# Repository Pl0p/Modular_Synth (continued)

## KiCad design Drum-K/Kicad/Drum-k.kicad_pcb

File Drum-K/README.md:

# Drum_K
Analogue drum kick

## Controls are :

 - Soft/Hard attack
 - Decay
 - Tune
 - Distortion
 - 

### Inputs

 - Kick trigger
 - [ ] Decay CV
 - [ ] Tune CV

# [Here is the schematic](https://github.com/Pl0p/Modular_Synth/blob/main/Drum-K/Drum-k.pdf)

### Front of the PCB 

### Back of the PCB

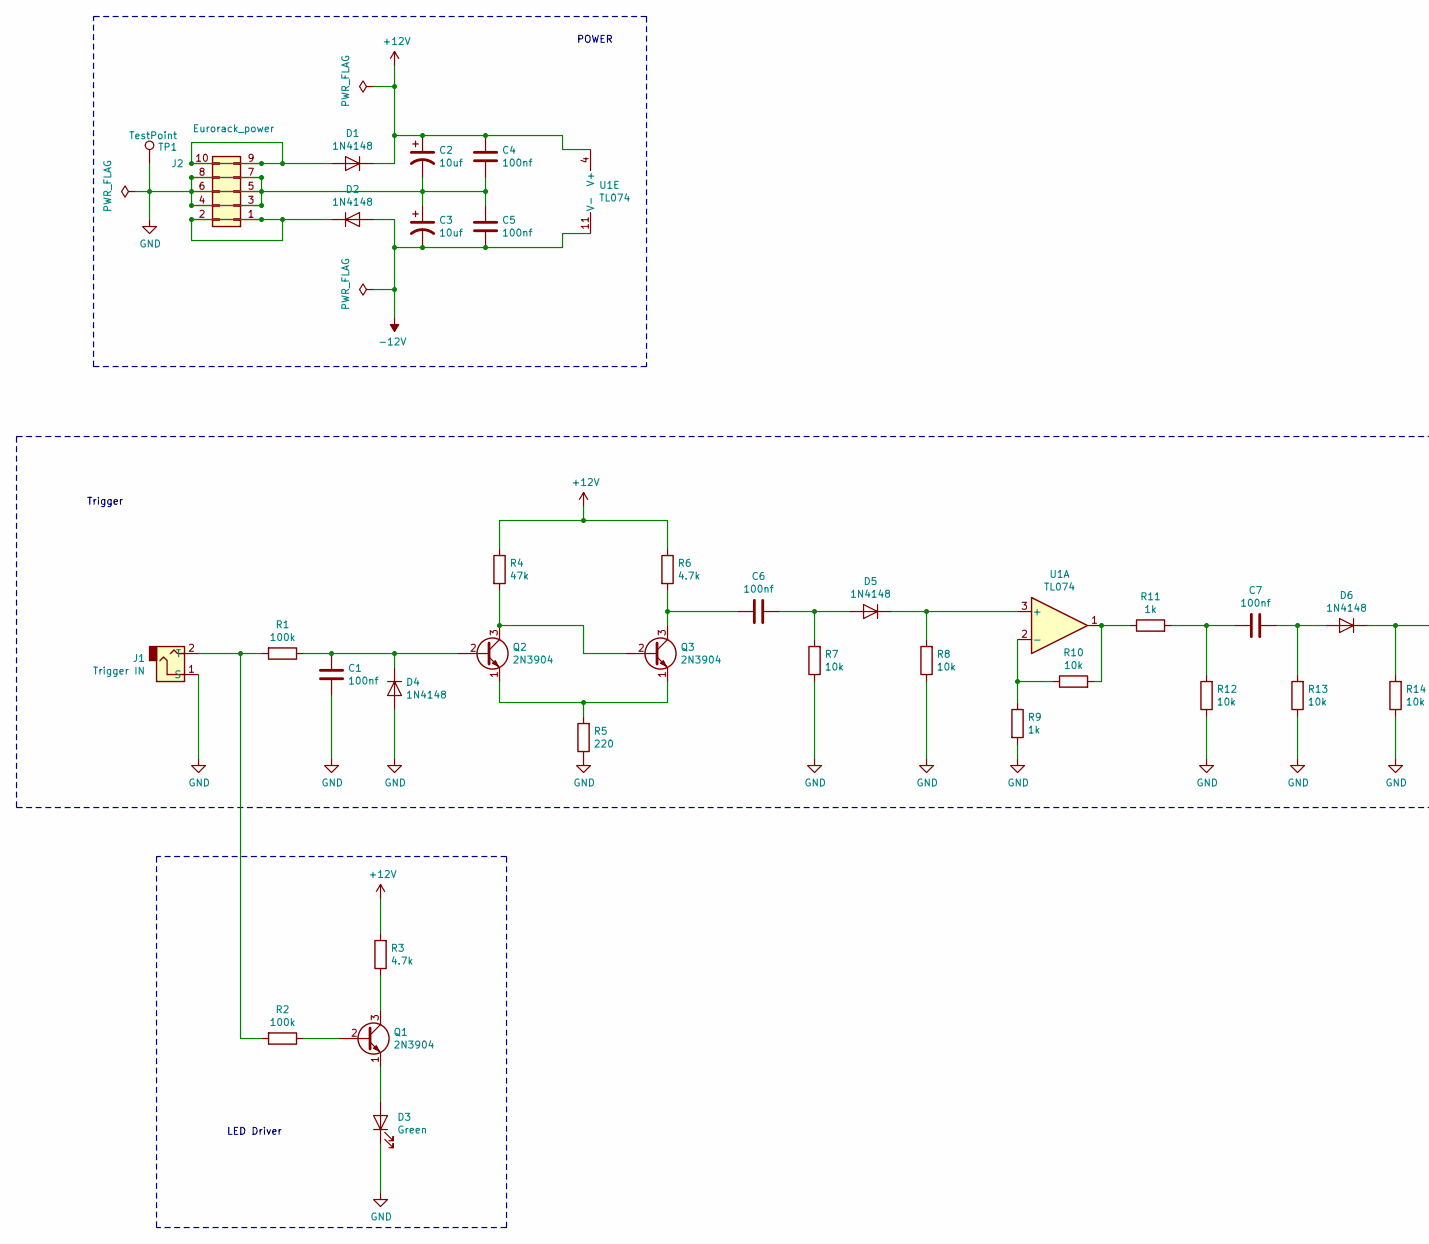
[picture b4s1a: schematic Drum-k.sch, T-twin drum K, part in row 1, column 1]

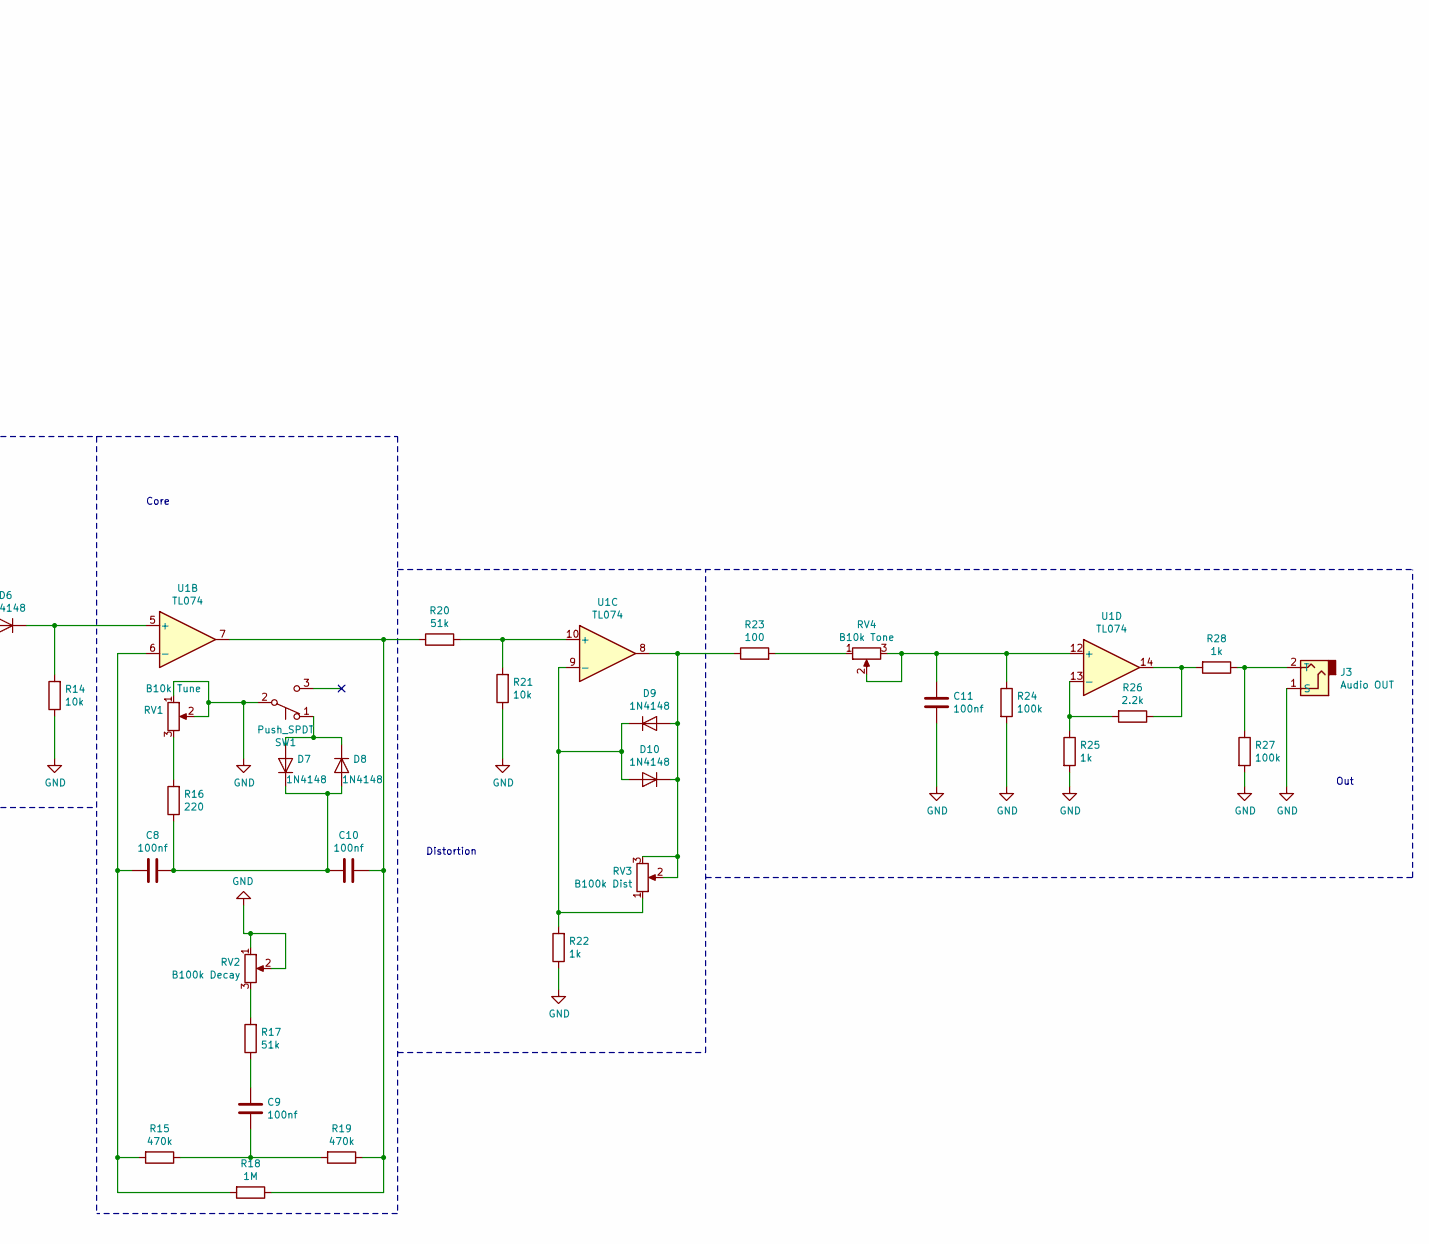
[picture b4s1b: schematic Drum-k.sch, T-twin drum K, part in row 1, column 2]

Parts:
C1, C4, C5, C6, C7, C8, C9, C10, C11: 100nf; C_Disc_(100nf_ceramique)
C2, C3: 10uf; C_Radial_10uf_50v(5*11)
D1, D2, D4, D5, D6, D7, D8, D9, D10: 1N4148; Diode1N4148
D3: Green; LED_5.0mm
J1: Trigger IN; SolderWirePad_1x02_Drill1.5mm
J2: Eurorack_power; 2X05_Power_conn
J3: Audio OUT; SolderWirePad_1x02_Drill1.5mm
Q1, Q2, Q3: 2N3904; Transistor
R1, R2, R24, R27: 100k; Resistance
R3, R6: 4.7k; Resistance
R4: 47k; Resistance
R5, R16: 220; Resistance
R7, R8, R10, R12, R13, R14, R21: 10k; Resistance
R9, R11, R22, R25, R28: 1k; Resistance
R15, R19: 470k; Resistance
R17, R20: 51k; Resistance
R18: 1M; Resistance
R23: 100; Resistance
R26: 2.2k; Resistance
RV1: B10k Tune; Pot_WH148-1A2
RV2: B100k Decay; Pot_WH148-1A2
RV3: B100k Dist; Pot_WH148-1A2
RV4: B10k Tone; Pot_WH148-1A2
SW1: Push_SPDT; SolderWirePad_1x02_+1NC_Drill1.5m
TP1: TestPoint; TestPoint_Pad_3.0x3.0mm
U1: TL074; DIP14-Socket

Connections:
+12V: C2.1, C4.1, D1.1 (K), R3.2, R4.1, R6.1, U1.4 (V+)
-12V: C3.2, C5.2, D2.2 (A), U1.11 (V-)
GND: C1.2, C2.2, C3.1, C4.2, C5.1, C11.2, D3.1 (K), D4.2 (A), J1.1 (S), J2.3, J2.4, J2.5, J2.6, J2.7, J2.8, J3.1 (S), R5.1, R7.1, R8.1, R9.2, R12.1, R13.1, R14.1, R21.1, R22.1, R24.2, R25.2, R27.2, RV1.1, RV1.2, RV2.1, RV2.2, SW1.2 (B), TP1.1
unnamed: C1.1, D4.1 (K), Q2.2 (B), R1.1
unnamed: C6.1, D5.2 (A), R7.2
unnamed: C6.2, Q3.3 (C), R6.2
unnamed: C7.1, D6.2 (A), R13.2
unnamed: C7.2, R11.2, R12.2
unnamed: C8.2, R15.2, R18.2, U1.6 (-)
unnamed: C9.1, R15.1, R19.2
unnamed: C9.2, R17.1
unnamed: C10.1, R18.1, R19.1, R20.1, U1.7
unnamed: C8.1, C10.2, D7.1 (K), D8.2 (A), R16.1
unnamed: C11.1, R24.1, RV4.2, RV4.3, U1.12 (+)
unnamed: D1.2 (A), J2.9, J2.10
unnamed: D2.1 (K), J2.1, J2.2
unnamed: D3.2 (A), Q1.1 (E)
unnamed: D5.1 (K), R8.2, U1.3 (+)
unnamed: D6.1 (K), R14.2, U1.5 (+)
unnamed: D7.2 (A), D8.1 (K), SW1.1 (A)
unnamed: D9.2 (A), D10.1 (K), R23.1, RV3.2, RV3.3, U1.8
unnamed: D9.1 (K), D10.2 (A), R22.2, RV3.1, U1.9 (-)
unnamed: J1.2 (T), R1.2, R2.2
unnamed: J3.2 (T), R27.1, R28.1
unnamed: Q1.2 (B), R2.1
unnamed: Q1.3 (C), R3.1
unnamed: Q2.1 (E), Q3.1 (E), R5.2
unnamed: Q2.3 (C), Q3.2 (B), R4.2
unnamed: R9.1, R10.1, U1.2 (-)
unnamed: R10.2, R11.1, U1.1
unnamed: R16.2, RV1.3
unnamed: R17.2, RV2.3
unnamed: R20.2, R21.2, U1.10 (+)
unnamed: R23.2, RV4.1
unnamed: R25.1, R26.2, U1.13 (-)
unnamed: R26.1, R28.2, U1.14

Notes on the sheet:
POWER
Trigger
LED Driver
Core
Distortion
Out

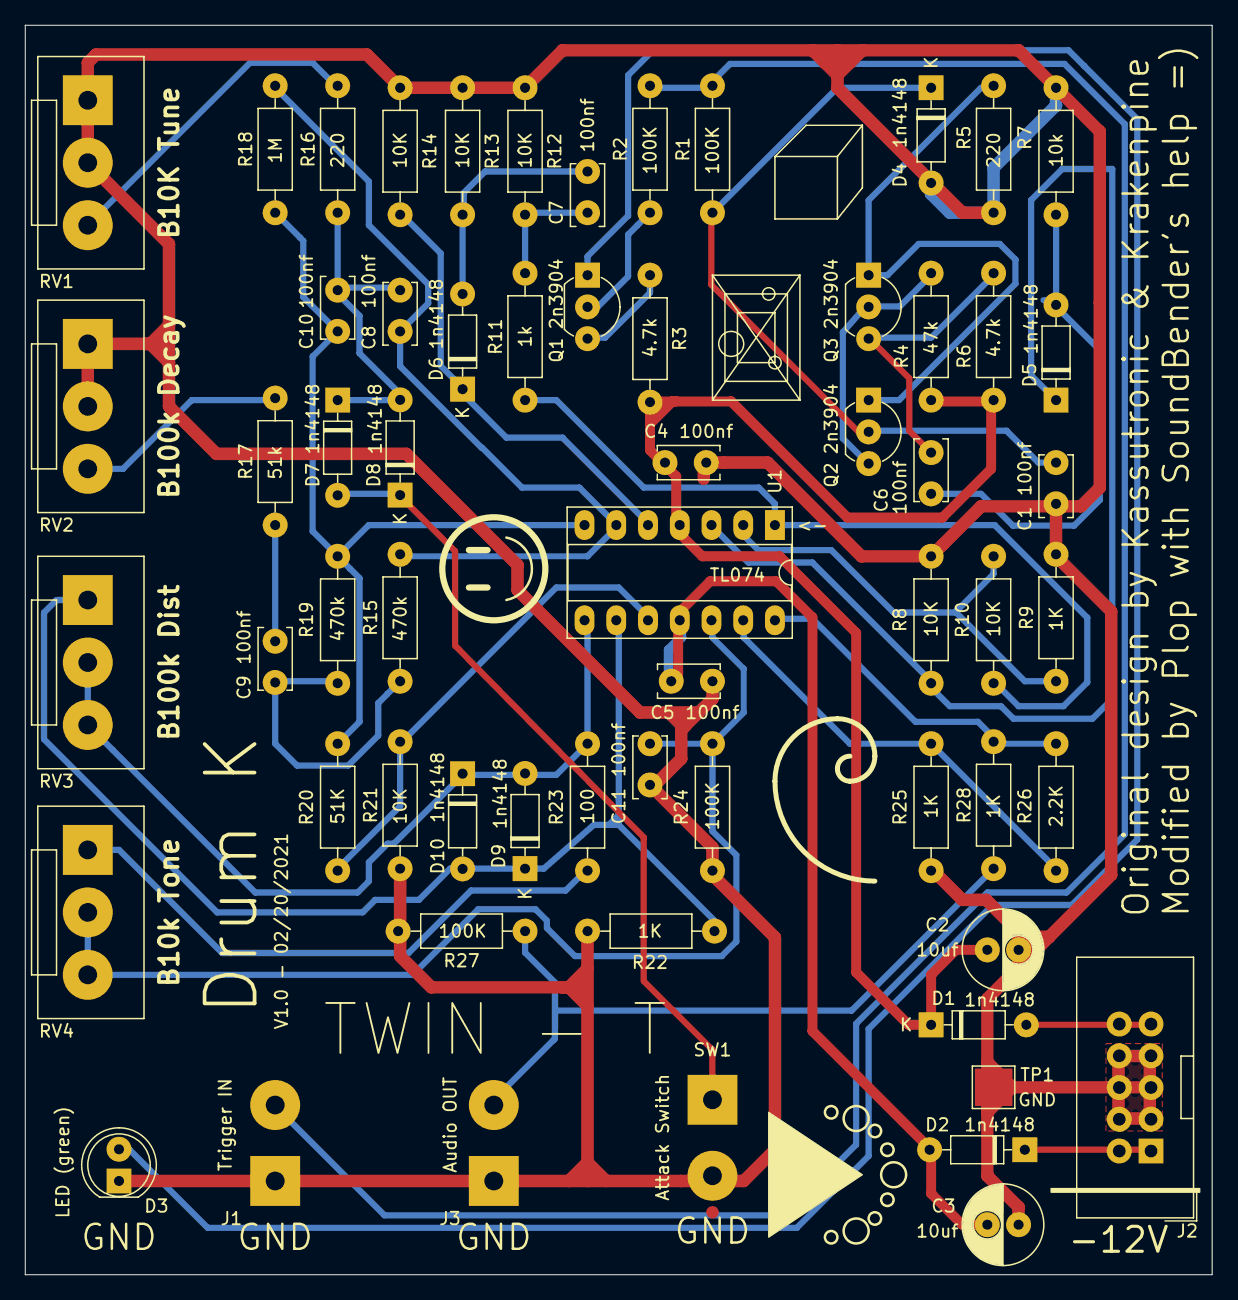
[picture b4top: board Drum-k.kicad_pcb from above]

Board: 2 copper layers, 95.0 x 100.0 mm, 62 parts (0 on the bottom side), 36 nets.

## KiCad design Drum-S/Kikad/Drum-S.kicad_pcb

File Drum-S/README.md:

# Drum_S Snare Drum

( /!\ NOT TESTED /!\ ) 
This is the second module i've done, the PCB is being delivered
 ( /!\ NOT TESTED /!\ )

## TODO 
 - [ ] Designing the panel
 - [ ] Noise gain

## Controls are :

 - Snare Decay
 - Noise Decay
 - Noise Tone
 - Drum Tune
 - Soft/Hard attack

### Inputs

 - Snare Trigger
 - [ ] Snare Decay CV
 - [ ] Tune CV
 - [ ] Volume

[Here is the schematic](https://github.com/Pl0p/Modular_Synth/blob/main/Drum-S/Drum-S.pdf)

### Front of the PCB 

### Back of the PCB

### Inspirations :
 [1](http://freenrg.info/Physics/Scalar_Vector_Pot_And_Rick_Andersen/Rick_Andersen_Noisegen.htm)
 [2](https://www.youtube.com/watch?v=px0D-ntx8Bk&t=311s)
 [3](https://www.youtube.com/watch?v=B8t38IFALTo&lc=UgyBIoDRvHR7-hIT61V4AaABAg.9JJD6eK1P_09JKVd2QjOil )

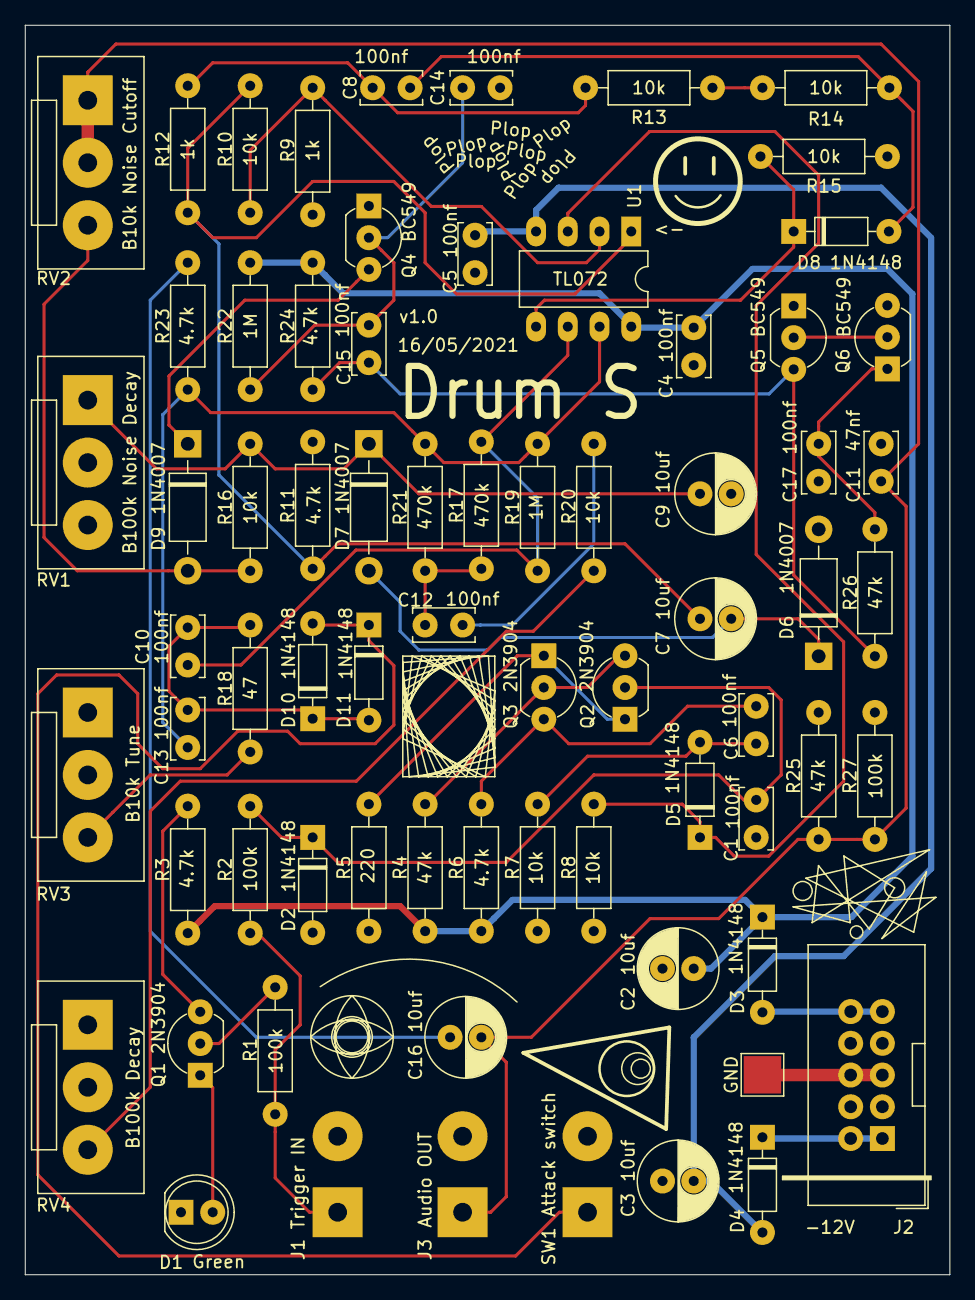
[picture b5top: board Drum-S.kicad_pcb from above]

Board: 2 copper layers, 74.0 x 100.0 mm, 71 parts (0 on the bottom side), 38 nets.

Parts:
C1, C4, C5, C6, C8, C10, C12, C13, C14, C15, C17: 100nf; C_Disc_(small_ceramique)
C2, C3, C7, C9, C16: 10uf; C_Radial_10uf_50v(5*11)
C11: 47nf; C_Disc_(small_ceramique)
D1: Green; LED_5.0mm
D2, D3, D4, D5, D8, D10, D11: 1N4148; Diode1N4148
D6, D7, D9: 1N4007; D_DO-41_SOD81_P10.16mm_Horizontal
GND: TestPoint; TestPoint_Pad_3.0x3.0mm
J1: Trigger IN; SolderWirePad_1x02_Drill1.5mm
J2: Eurorack_power; 2X05_Power_conn
J3: Audio OUT; SolderWirePad_1x02_Drill1.5mm
Q1, Q2, Q3: 2N3904; 2n3904
Q4, Q5, Q6: BC549
R1, R2, R27: 100k; Resistance
R3, R6, R11, R23, R24: 4.7k; Resistance
R4, R25, R26: 47k; Resistance
R5: 220; Resistance
R7, R8, R10, R13, R14, R15, R16, R20: 10k; Resistance
R9, R12: 1k; Resistance
R17, R21: 470k; Resistance
R18: 47; Resistance
R19, R22: 1M; Resistance
RV1: B100k Noise Decay; Pot_WH148-1A2
RV2: B10k Noise Cutoff; Pot_WH148-1A2
RV3: B10k Tune; Pot_WH148-1A2
RV4: B100k Decay; Pot_WH148-1A2
SW1: Attack switch; SolderWirePad_1x02_+1NC_Drill1.5m
U1: TL072; DIP8_Socket

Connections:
+12V: C2.1, C4.1, D3.1, R3.2, R4.1, R6.1, R22.1, R24.1, U1.8
-12V: C3.2, C5.2, D4.2, U1.4
GND: C1.2, C2.2, C3.1, C4.2, C5.1, C9.2, C11.2, C14.1, C17.1, D1.1, D2.2, D6.2, GND.1, J1.2, J2.3, J2.4, J2.5, J2.6, J2.7, J2.8, J3.2, Q4.3, Q5.3, R5.1, R7.1, R8.1, R9.2, R11.2, R13.1, R14.1, R15.1, R25.1, R27.1, RV1.2, RV1.3, RV3.1, RV3.2, RV4.1, RV4.2, SW1.2
unnamed: C1.1, D2.1, Q2.2, R2.1
unnamed: C6.1, D5.2, R7.2
unnamed: C6.2, Q3.3, R6.2
unnamed: C7.1, R10.2, R11.1, R12.1, U1.1
unnamed: C7.2, D6.1, D7.2
unnamed: C8.1, D8.2, R14.2
unnamed: C8.2, R12.2, R13.2
unnamed: C9.1, D7.1, R16.1, RV1.1
unnamed: C10.1, C13.2, D10.1, D11.2, R18.1
unnamed: C10.2, R17.2, R19.2, U1.6
unnamed: C11.1, C16.2, J3.1, R25.2, R27.2, RV2.1, RV2.2
unnamed: C12.1, R17.1, R21.2
unnamed: C12.2, R20.1
unnamed: C13.1, R19.1, R21.1, R23.2, U1.7
unnamed: C14.2, C15.1, Q4.2, R22.2
unnamed: C15.2, Q5.1, R24.2, R26.1
unnamed: C16.1, R23.1
unnamed: C17.2, Q6.3, R26.2
unnamed: D1.2, Q1.1
unnamed: D3.2, J2.9, J2.10
unnamed: D4.1, J2.1, J2.2
unnamed: D5.1, R8.2, U1.3
unnamed: D8.1, R15.2, U1.5
unnamed: D9.1, Q4.1
unnamed: D9.2, R16.2, RV2.3
unnamed: D10.2, D11.1, SW1.1
unnamed: J1.1, R1.2, R2.2
unnamed: Q1.2, R1.1
unnamed: Q1.3, R3.1
unnamed: Q2.1, Q3.1, R5.2
unnamed: Q2.3, Q3.2, R4.2
unnamed: Q5.2, Q6.2
unnamed: R9.1, R10.1, U1.2
unnamed: R18.2, RV3.3
unnamed: R20.2, RV4.3

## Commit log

2021-06-08 Kick drum module
2021-06-08 Snare drum module
2021-06-08 Hi-Hats drum module
2021-06-08 Gate sequencer
2021-06-08 Update opensource list
2021-06-08 LessMess
2021-06-09 Start to alphabetise
2021-06-09 Alphabetise github section
2021-06-11 Hi-Hat module
2021-07-02 Adding tim stinchcombe
2021-07-30 morocco dave added
2021-08-10 Drum-H
2021-08-22 Adding Syinsi modules
2021-08-22 Adding Niklas Rönnberg
2021-08-25 Adding schmitzbits's circuits
2021-08-25 Multiple entry
2021-11-23 New github repo
2021-11-23 New entry
    + https://github.com/noisereap/schema-cave
    + https://github.com/wntrblm
2021-11-23 New entry in the todo list
2021-12-08 adding naokiiwakami to the github repo
2021-12-22 New entry : Synthr
2021-12-22 More stuff to do
2021-12-27 New entry in github repo
    adding https://github.com/polykit
2021-12-27 Rename List_by_function.md to List_of_modules_by_functions.md
2021-12-27 Rename Open-source_list.md to List_of_open-source_makers.md
2023-03-11 Update List_of_open-source_makers.md
    Adding MeeBilt (tkilla64) to the list
    https://github.com/tkilla64/eurorack
2023-03-11 Update List_of_modules_by_functions.md
    One more entry in the todo list. YAAY !
2023-04-15 Create Drum-K MkII
2023-04-15 New drum kick
2023-04-15 New Drum-Kick
2023-04-15 New Drum-K
2023-04-15 Photos
2023-04-15 Photos =)
2023-04-15 typo
2023-04-15 Old version
2023-04-15 New Drum K
